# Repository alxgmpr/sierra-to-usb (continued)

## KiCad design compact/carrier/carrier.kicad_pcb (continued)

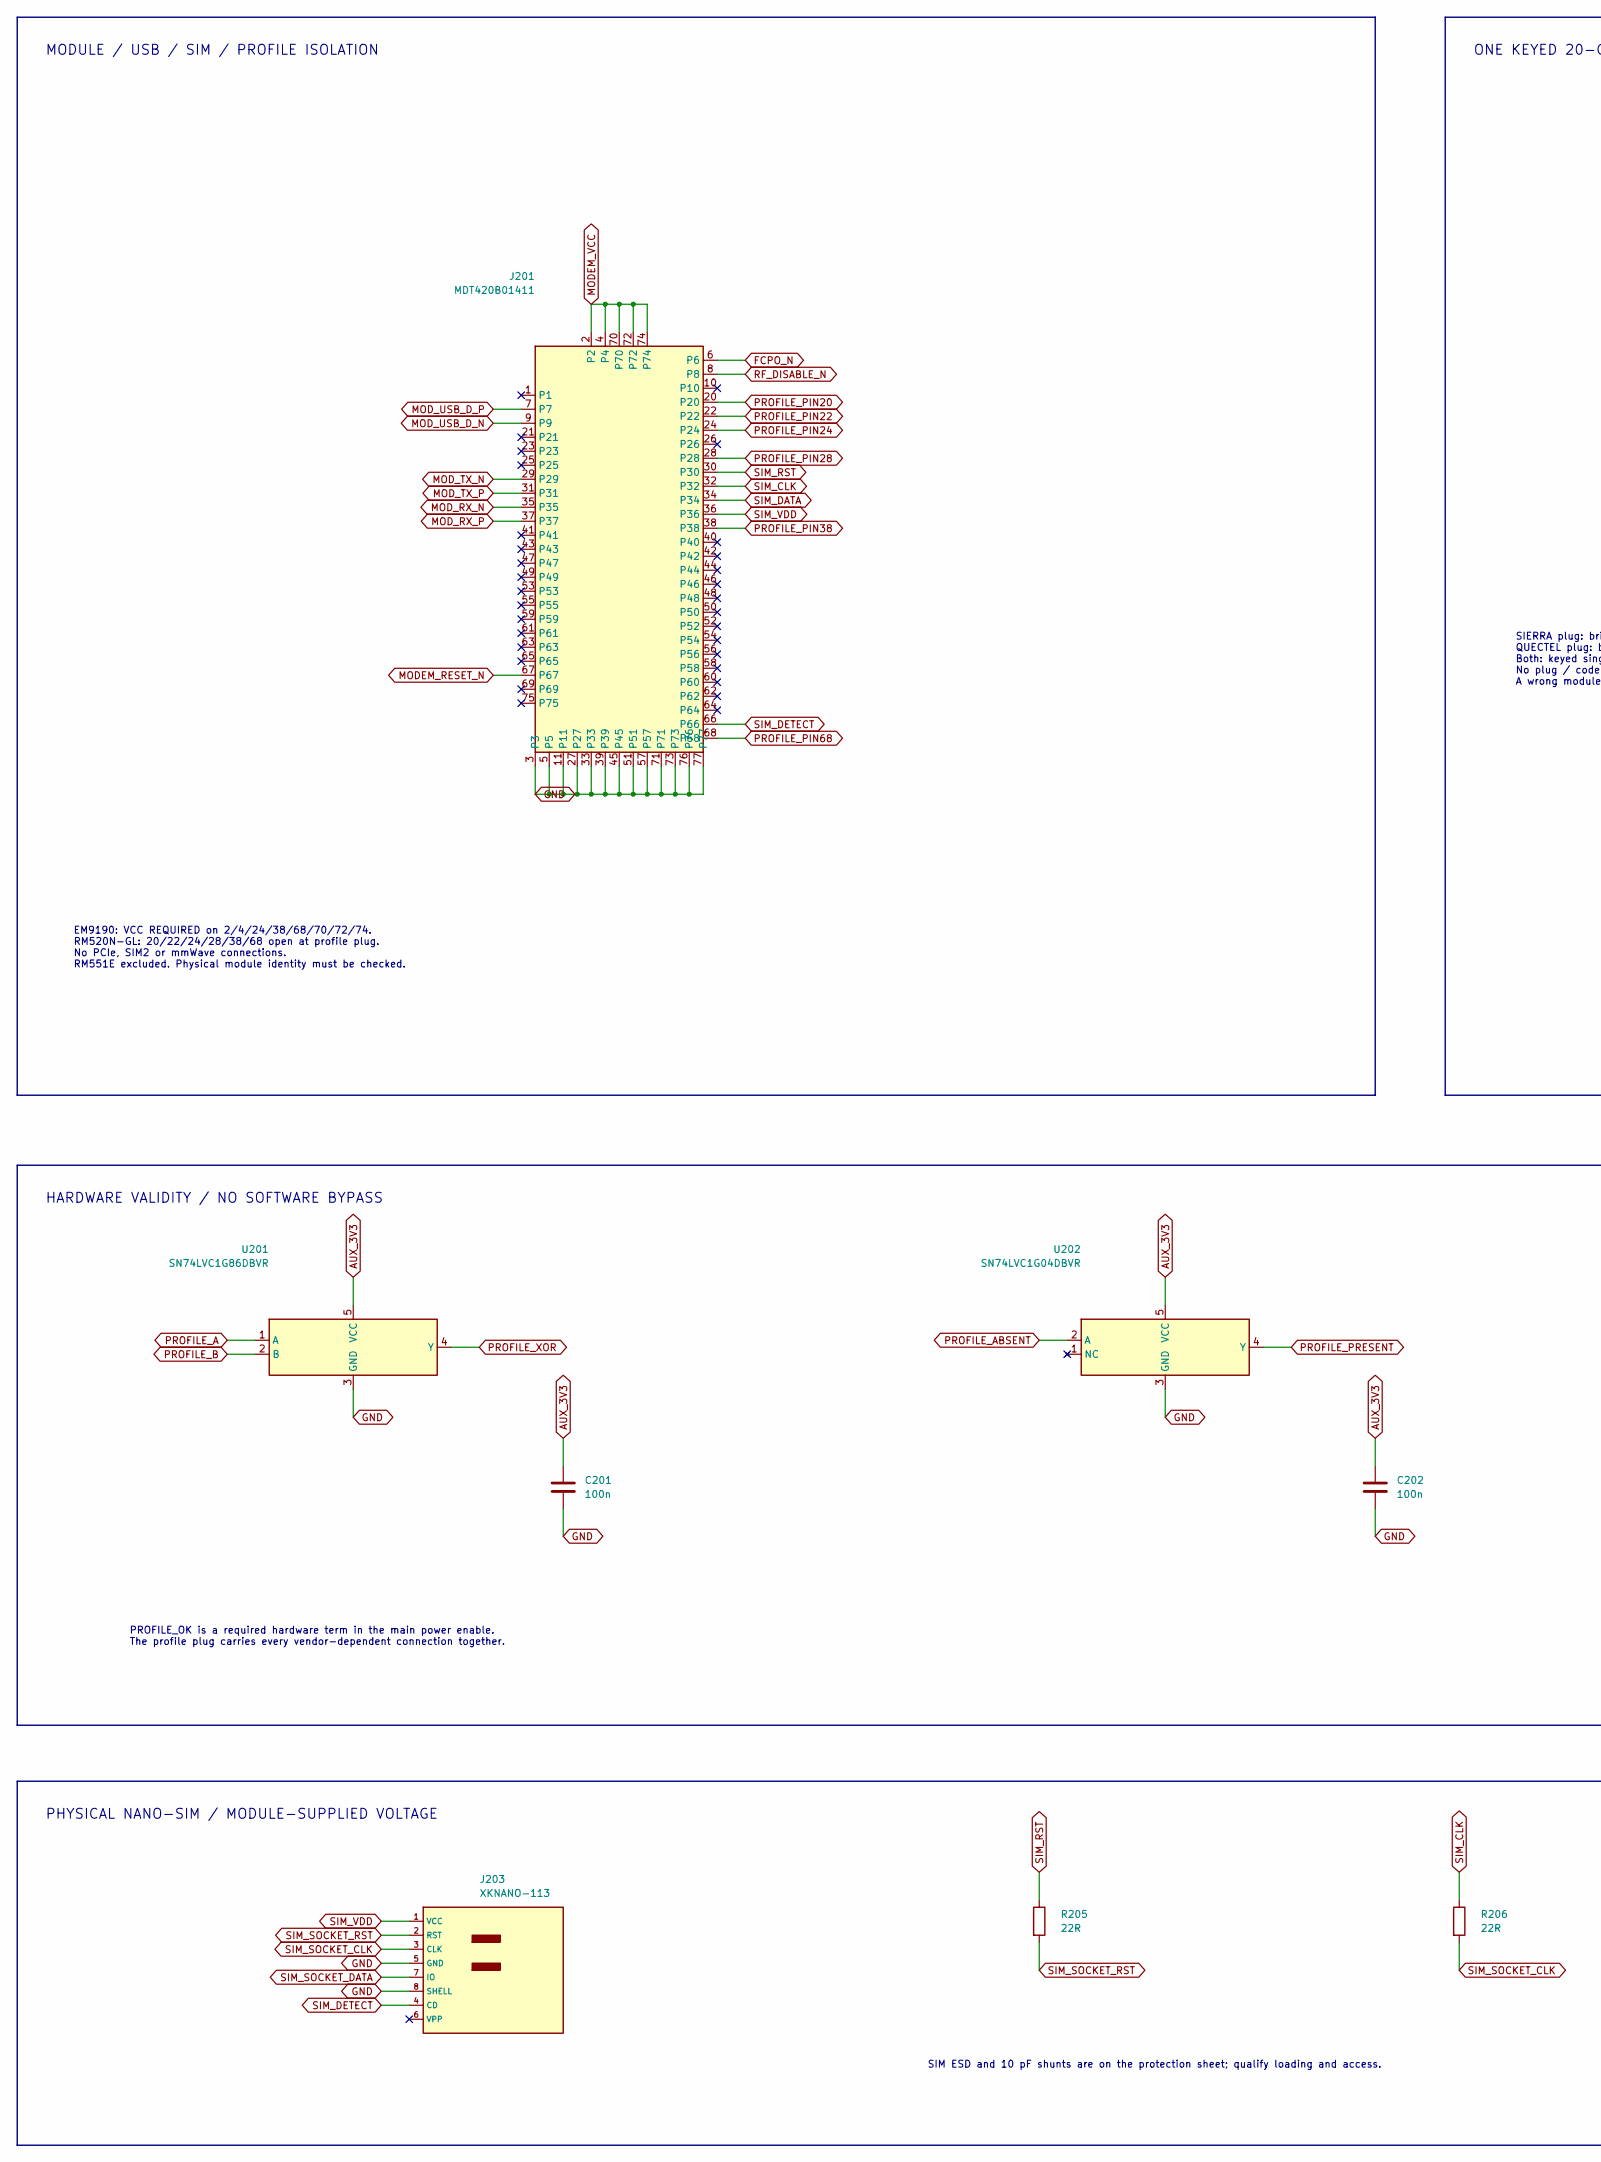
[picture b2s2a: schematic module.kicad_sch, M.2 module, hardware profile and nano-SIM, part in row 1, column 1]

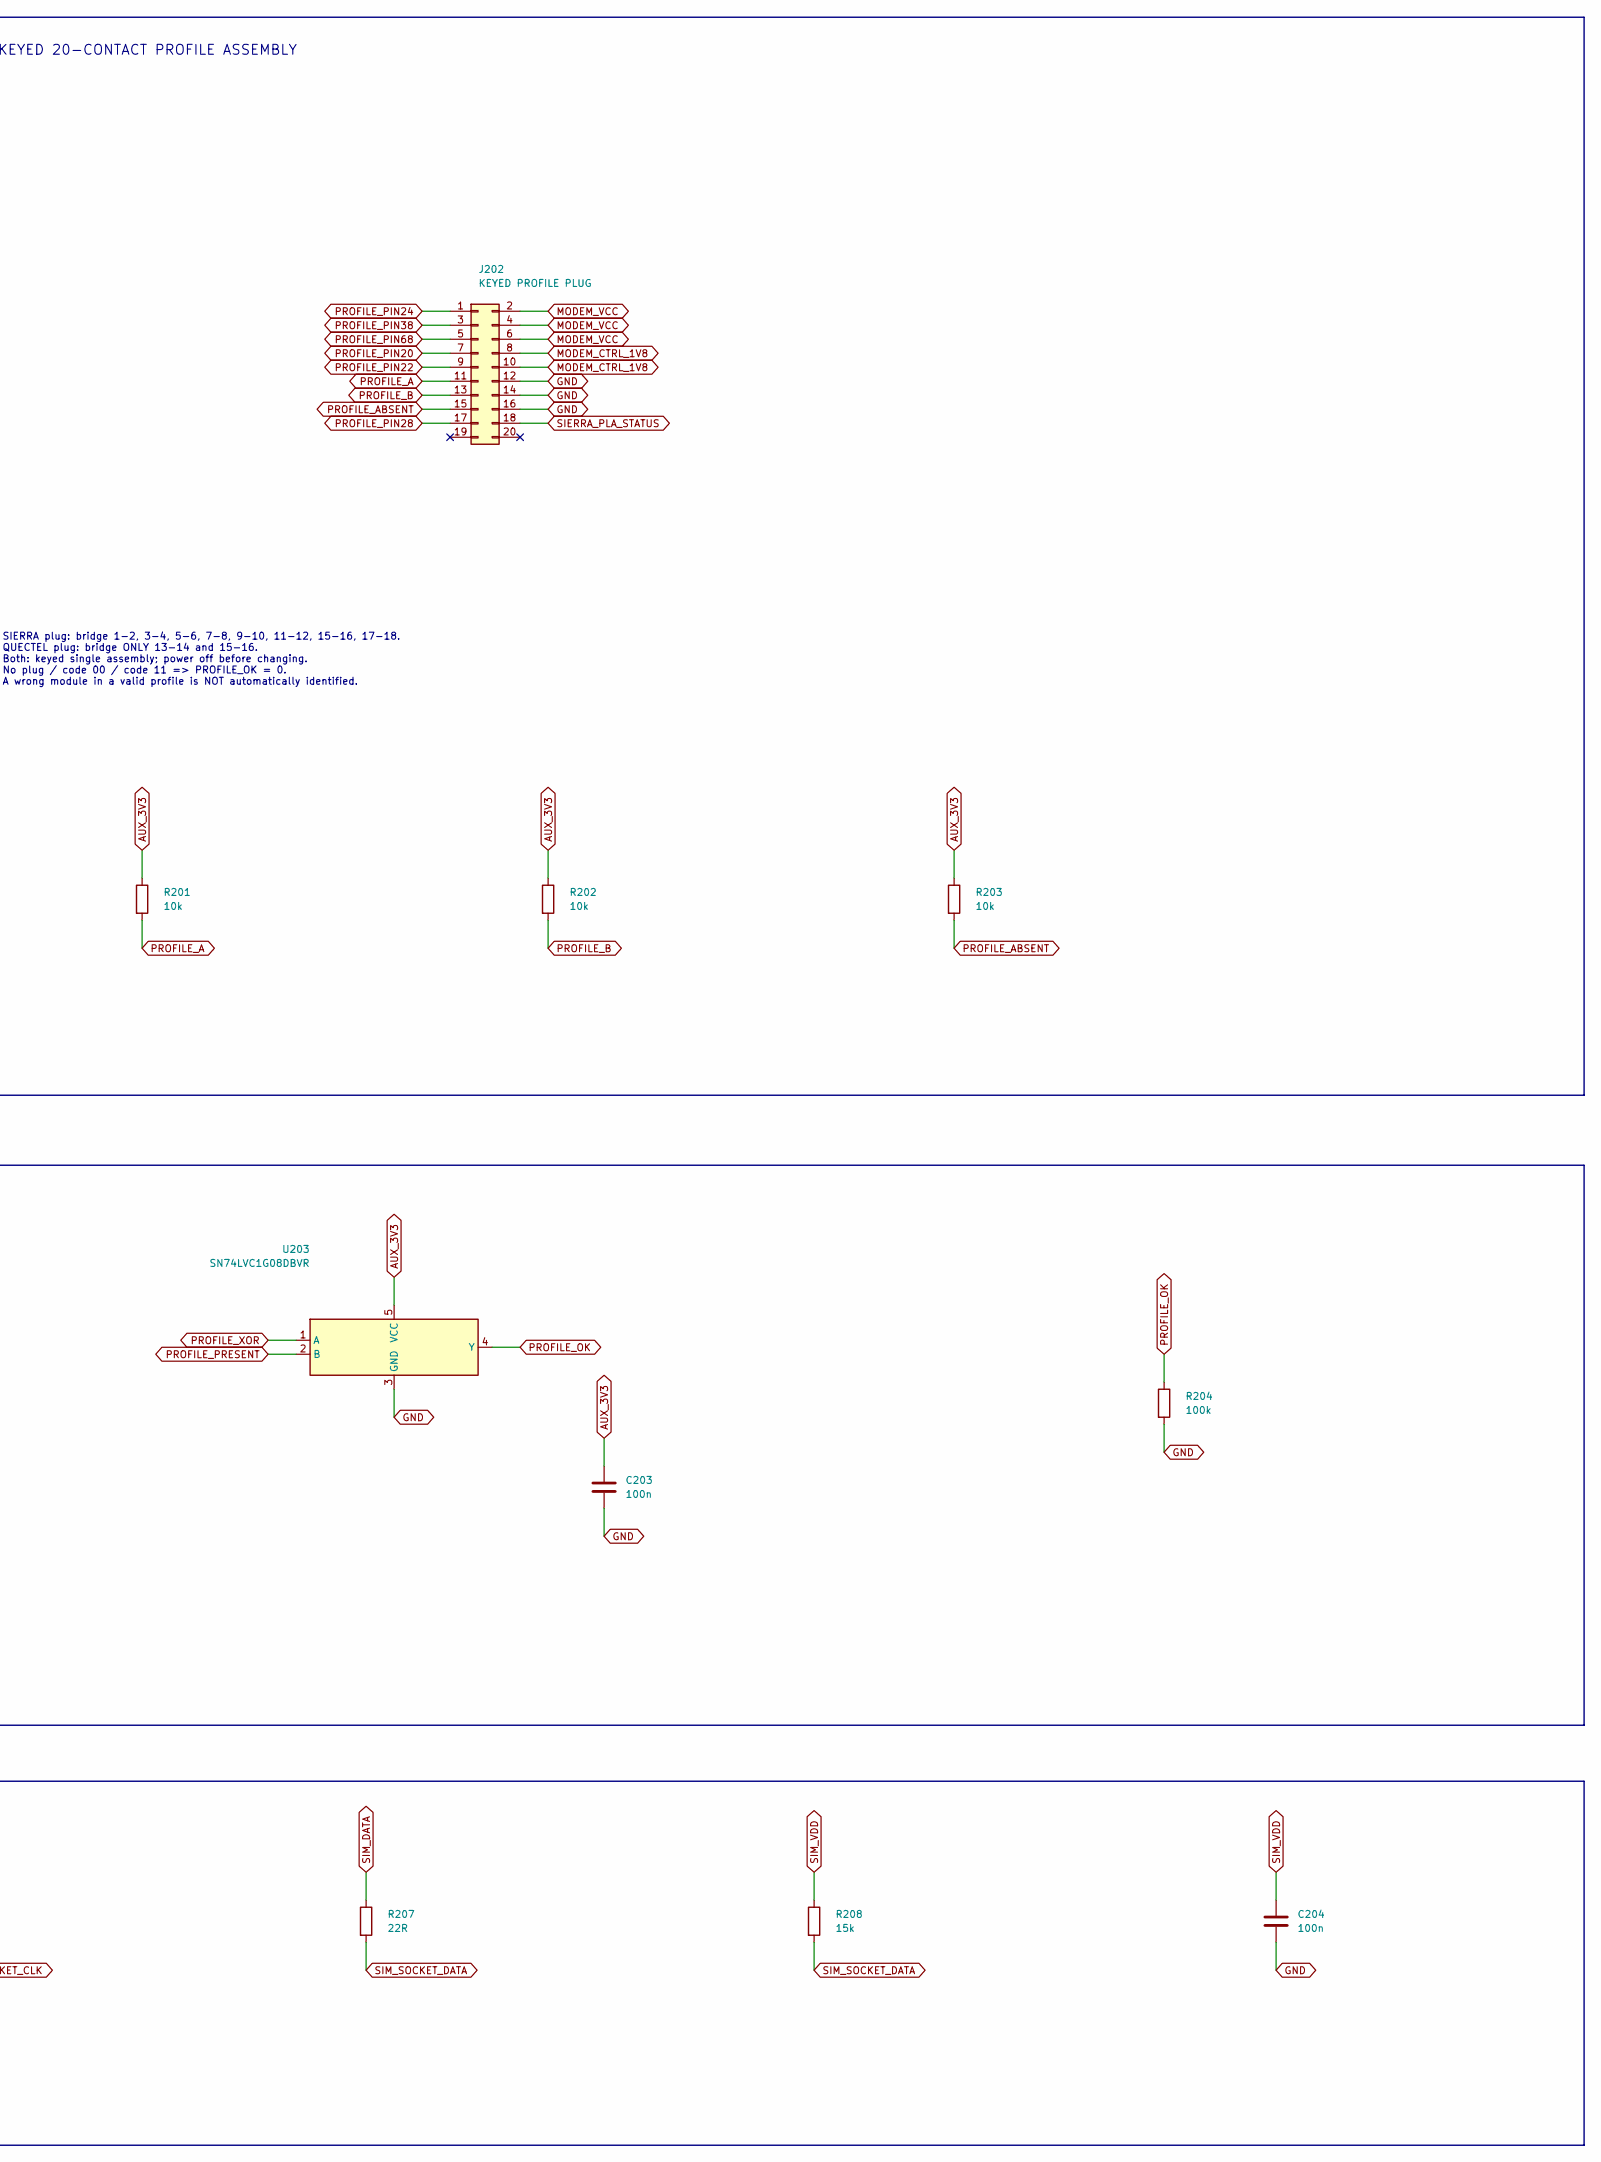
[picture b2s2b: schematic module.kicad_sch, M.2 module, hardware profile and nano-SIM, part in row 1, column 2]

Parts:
C201, C202, C203, C204: 100n; C_0805_2012Metric; MPN C2012X7R1H104K085AA
J201: MDT420B01411; M2_B_Amphenol_MDT420_1A; MPN MDT420B01411
J202: KEYED PROFILE PLUG; IDC_3M_N2520_6002_RB; MPN N2520-6002-RB
J203: XKNANO-113; NanoSIM_XKB_XKNANO-113; MPN XKNANO-113; LCSC C381071
R201, R202, R203: 10k; R_0603_1608Metric; MPN RC0603FR-0710KL
R204: 100k; R_0603_1608Metric; MPN RC0603FR-07100KL
R205, R206, R207: 22R; R_0603_1608Metric; MPN ERJ-3EKF22R0V
R208: 15k; R_0603_1608Metric; MPN RC0603FR-0715KL
U201: SN74LVC1G86DBVR; SOT-23-5; MPN SN74LVC1G86DBVR
U202: SN74LVC1G04DBVR; SOT-23-5; MPN SN74LVC1G04DBVR
U203: SN74LVC1G08DBVR; SOT-23-5; MPN SN74LVC1G08DBVR

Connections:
AUX_3V3: C201.1, C202.1, C203.1, R201.1, R202.1, R203.1, U201.5 (VCC), U202.5 (VCC), U203.5 (VCC); also elsewhere on the board
FCPO_N: J201.6; also elsewhere on the board
GND: C201.2, C202.2, C203.2, C204.2, J201.3, J201.5, J201.11, J201.27, J201.33, J201.39, J201.45, J201.51, J201.57, J201.71, J201.73, J201.76, J201.77, J202.12, J202.14, J202.16, J203.5 (GND), J203.8 (SHELL), R204.2, U201.3 (GND), U202.3 (GND), U203.3 (GND); also elsewhere on the board
MODEM_CTRL_1V8: J202.8, J202.10; also elsewhere on the board
MODEM_RESET_N: J201.67; also elsewhere on the board
MODEM_VCC: J201.2, J201.4, J201.70, J201.72, J201.74, J202.2, J202.4, J202.6; also elsewhere on the board
MOD_RX_N: J201.35; also elsewhere on the board
MOD_RX_P: J201.37; also elsewhere on the board
MOD_TX_N: J201.29; also elsewhere on the board
MOD_TX_P: J201.31; also elsewhere on the board
MOD_USB_D_N: J201.9; also elsewhere on the board
MOD_USB_D_P: J201.7; also elsewhere on the board
PROFILE_A: J202.11, R201.2, U201.1 (A)
PROFILE_ABSENT: J202.15, R203.2, U202.2 (A)
PROFILE_B: J202.13, R202.2, U201.2 (B)
PROFILE_OK: R204.1, U203.4 (Y); also elsewhere on the board
PROFILE_PIN20: J201.20, J202.7
PROFILE_PIN22: J201.22, J202.9
PROFILE_PIN24: J201.24, J202.1
PROFILE_PIN28: J201.28, J202.17
PROFILE_PIN38: J201.38, J202.3
PROFILE_PIN68: J201.68, J202.5
PROFILE_PRESENT: U202.4 (Y), U203.2 (B)
PROFILE_XOR: U201.4 (Y), U203.1 (A)
RF_DISABLE_N: J201.8; also elsewhere on the board
SIERRA_PLA_STATUS: J202.18; also elsewhere on the board
SIM_CLK: J201.32, R206.1
SIM_DATA: J201.34, R207.1
SIM_DETECT: J201.66, J203.4 (CD)
SIM_RST: J201.30, R205.1
SIM_SOCKET_CLK: J203.3 (CLK), R206.2; also elsewhere on the board
SIM_SOCKET_DATA: J203.7 (IO), R207.2, R208.2; also elsewhere on the board
SIM_SOCKET_RST: J203.2 (RST), R205.2; also elsewhere on the board
SIM_VDD: C204.1, J201.36, J203.1 (VCC), R208.1; also elsewhere on the board

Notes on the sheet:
MODULE / USB / SIM / PROFILE ISOLATION
EM9190: VCC REQUIRED on 2/4/24/38/68/70/72/74. RM520N-GL: 20/22/24/28/38/68 open at profile plug. No PCIe, SIM2 or mmWave connections. RM551E excluded. Physical module identity must be checked.
ONE KEYED 20-CONTACT PROFILE ASSEMBLY
SIERRA plug: bridge 1-2, 3-4, 5-6, 7-8, 9-10, 11-12, 15-16, 17-18. QUECTEL plug: bridge ONLY 13-14 and 15-16. Both: keyed single assembly; power off before changing. No plug / code 00 / code 11 => PROFILE_OK = 0. A wrong module in a valid profile is NOT automatically identified.
HARDWARE VALIDITY / NO SOFTWARE BYPASS
PROFILE_OK is a required hardware term in the main power enable. The profile plug carries every vendor-dependent connection together.
PHYSICAL NANO-SIM / MODULE-SUPPLIED VOLTAGE
SIM ESD and 10 pF shunts are on the protection sheet; qualify loading and access.

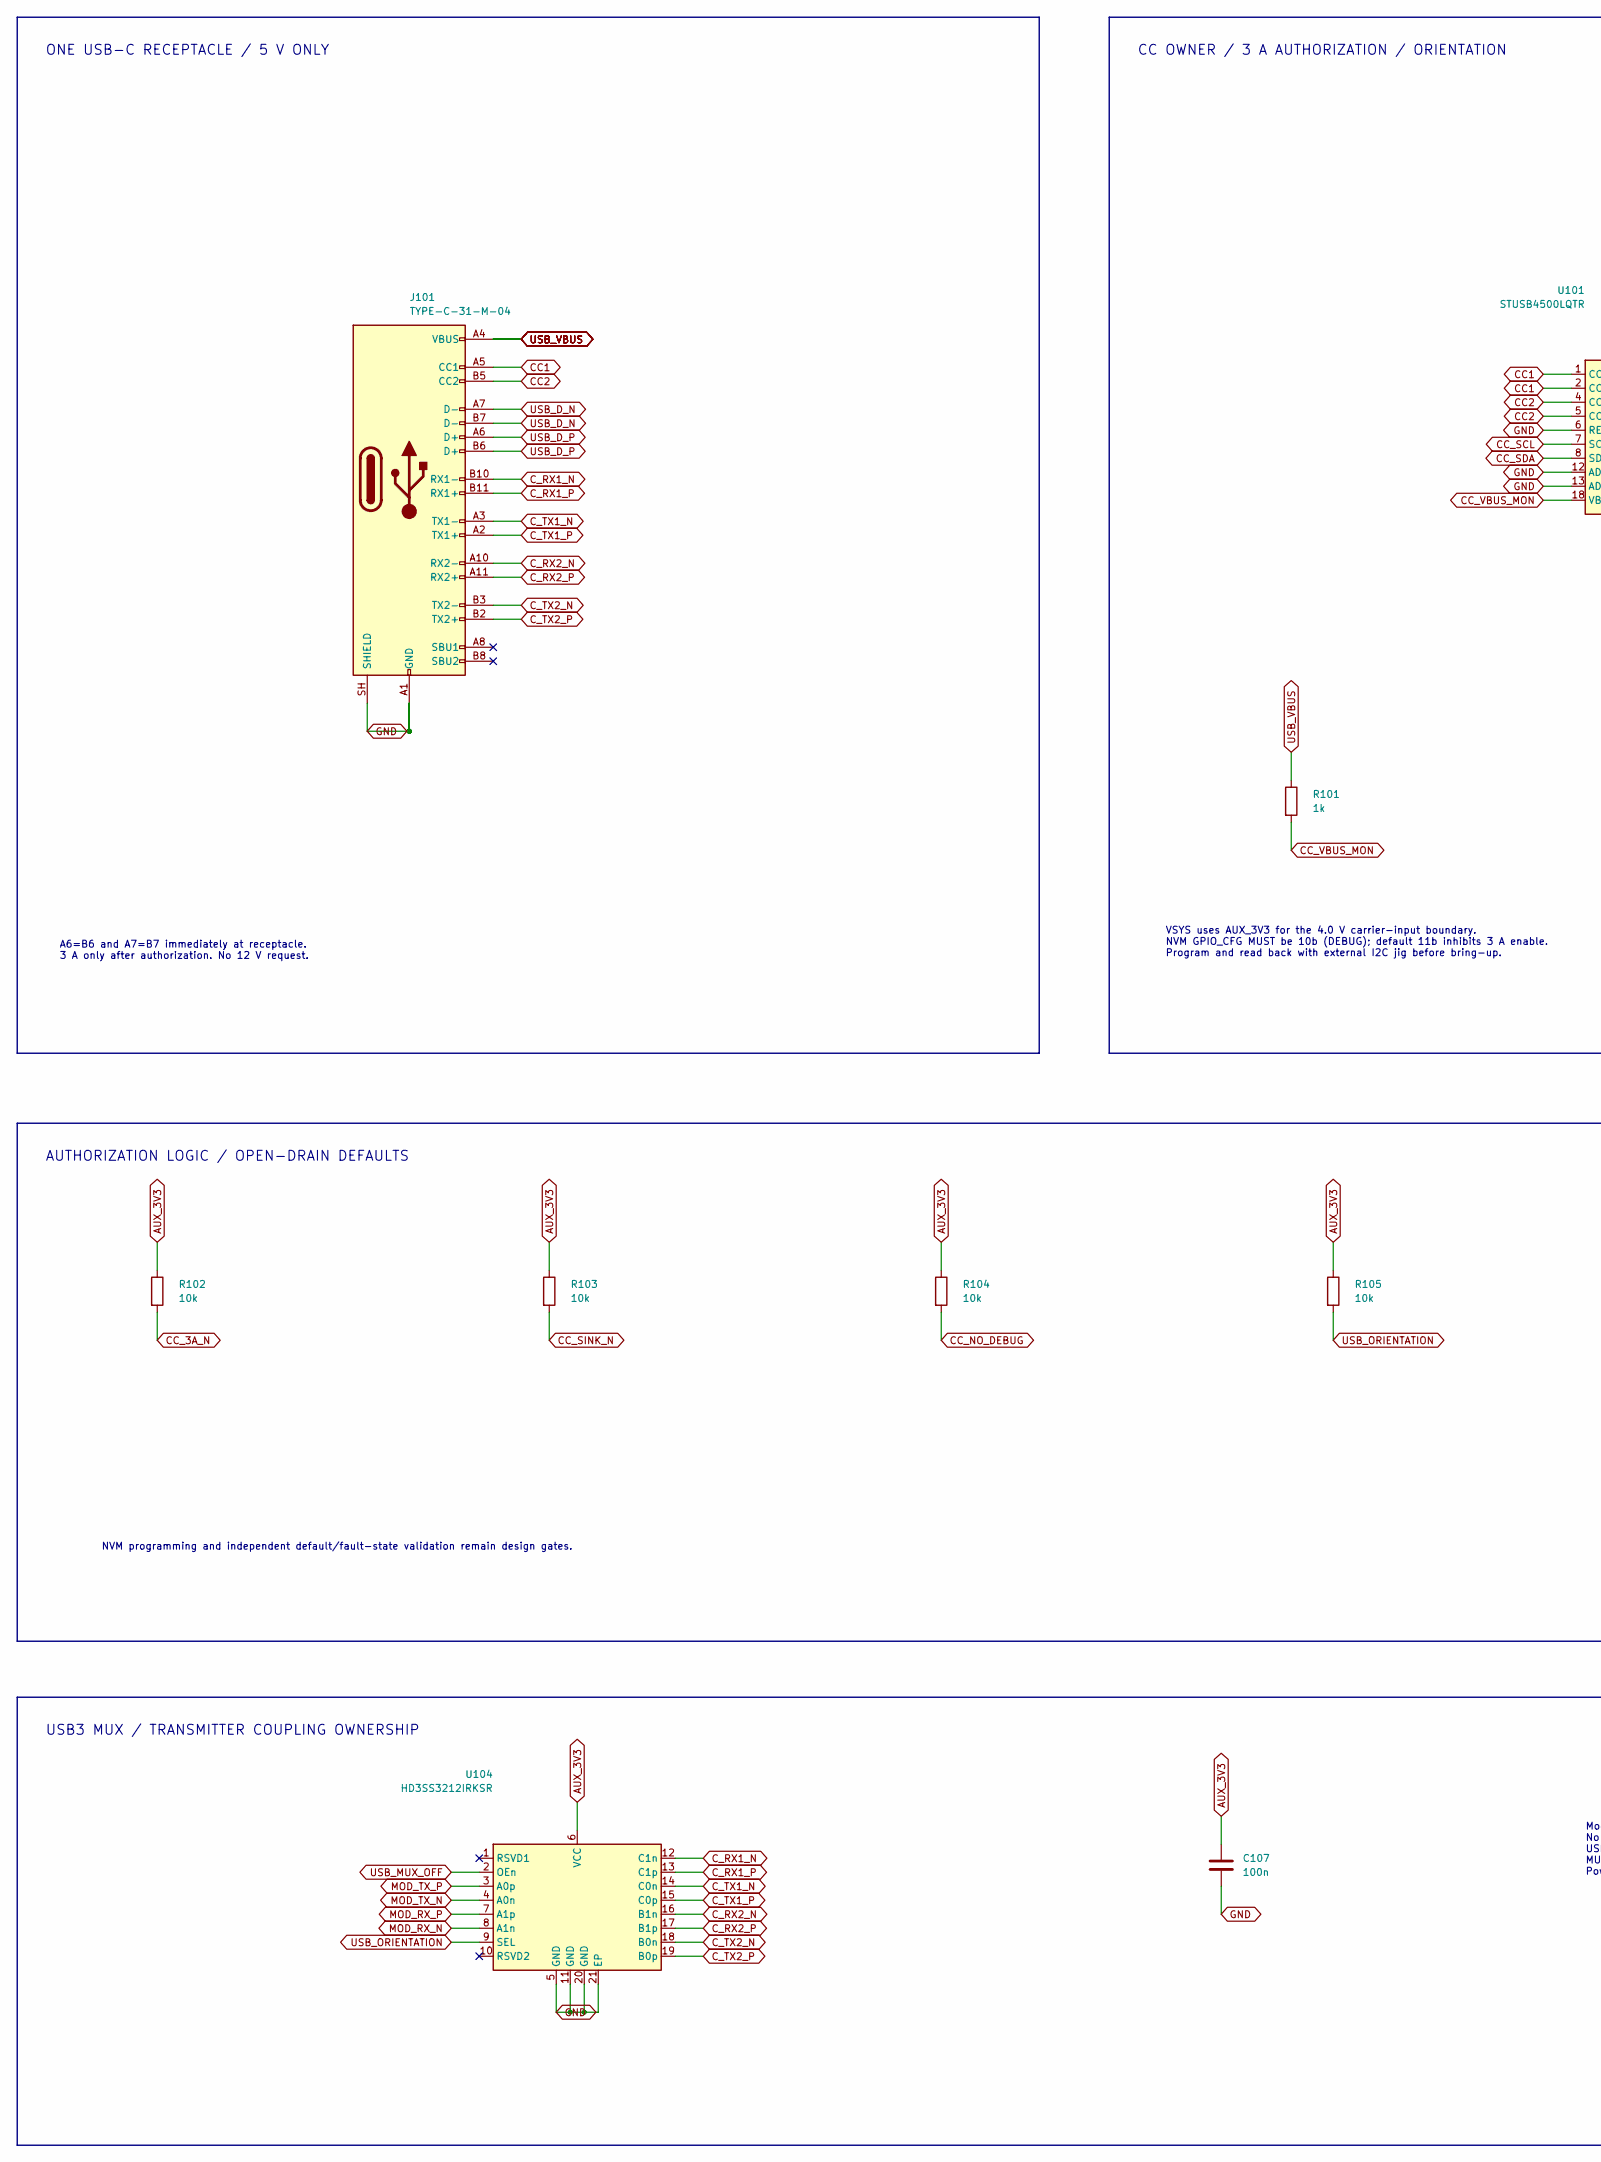
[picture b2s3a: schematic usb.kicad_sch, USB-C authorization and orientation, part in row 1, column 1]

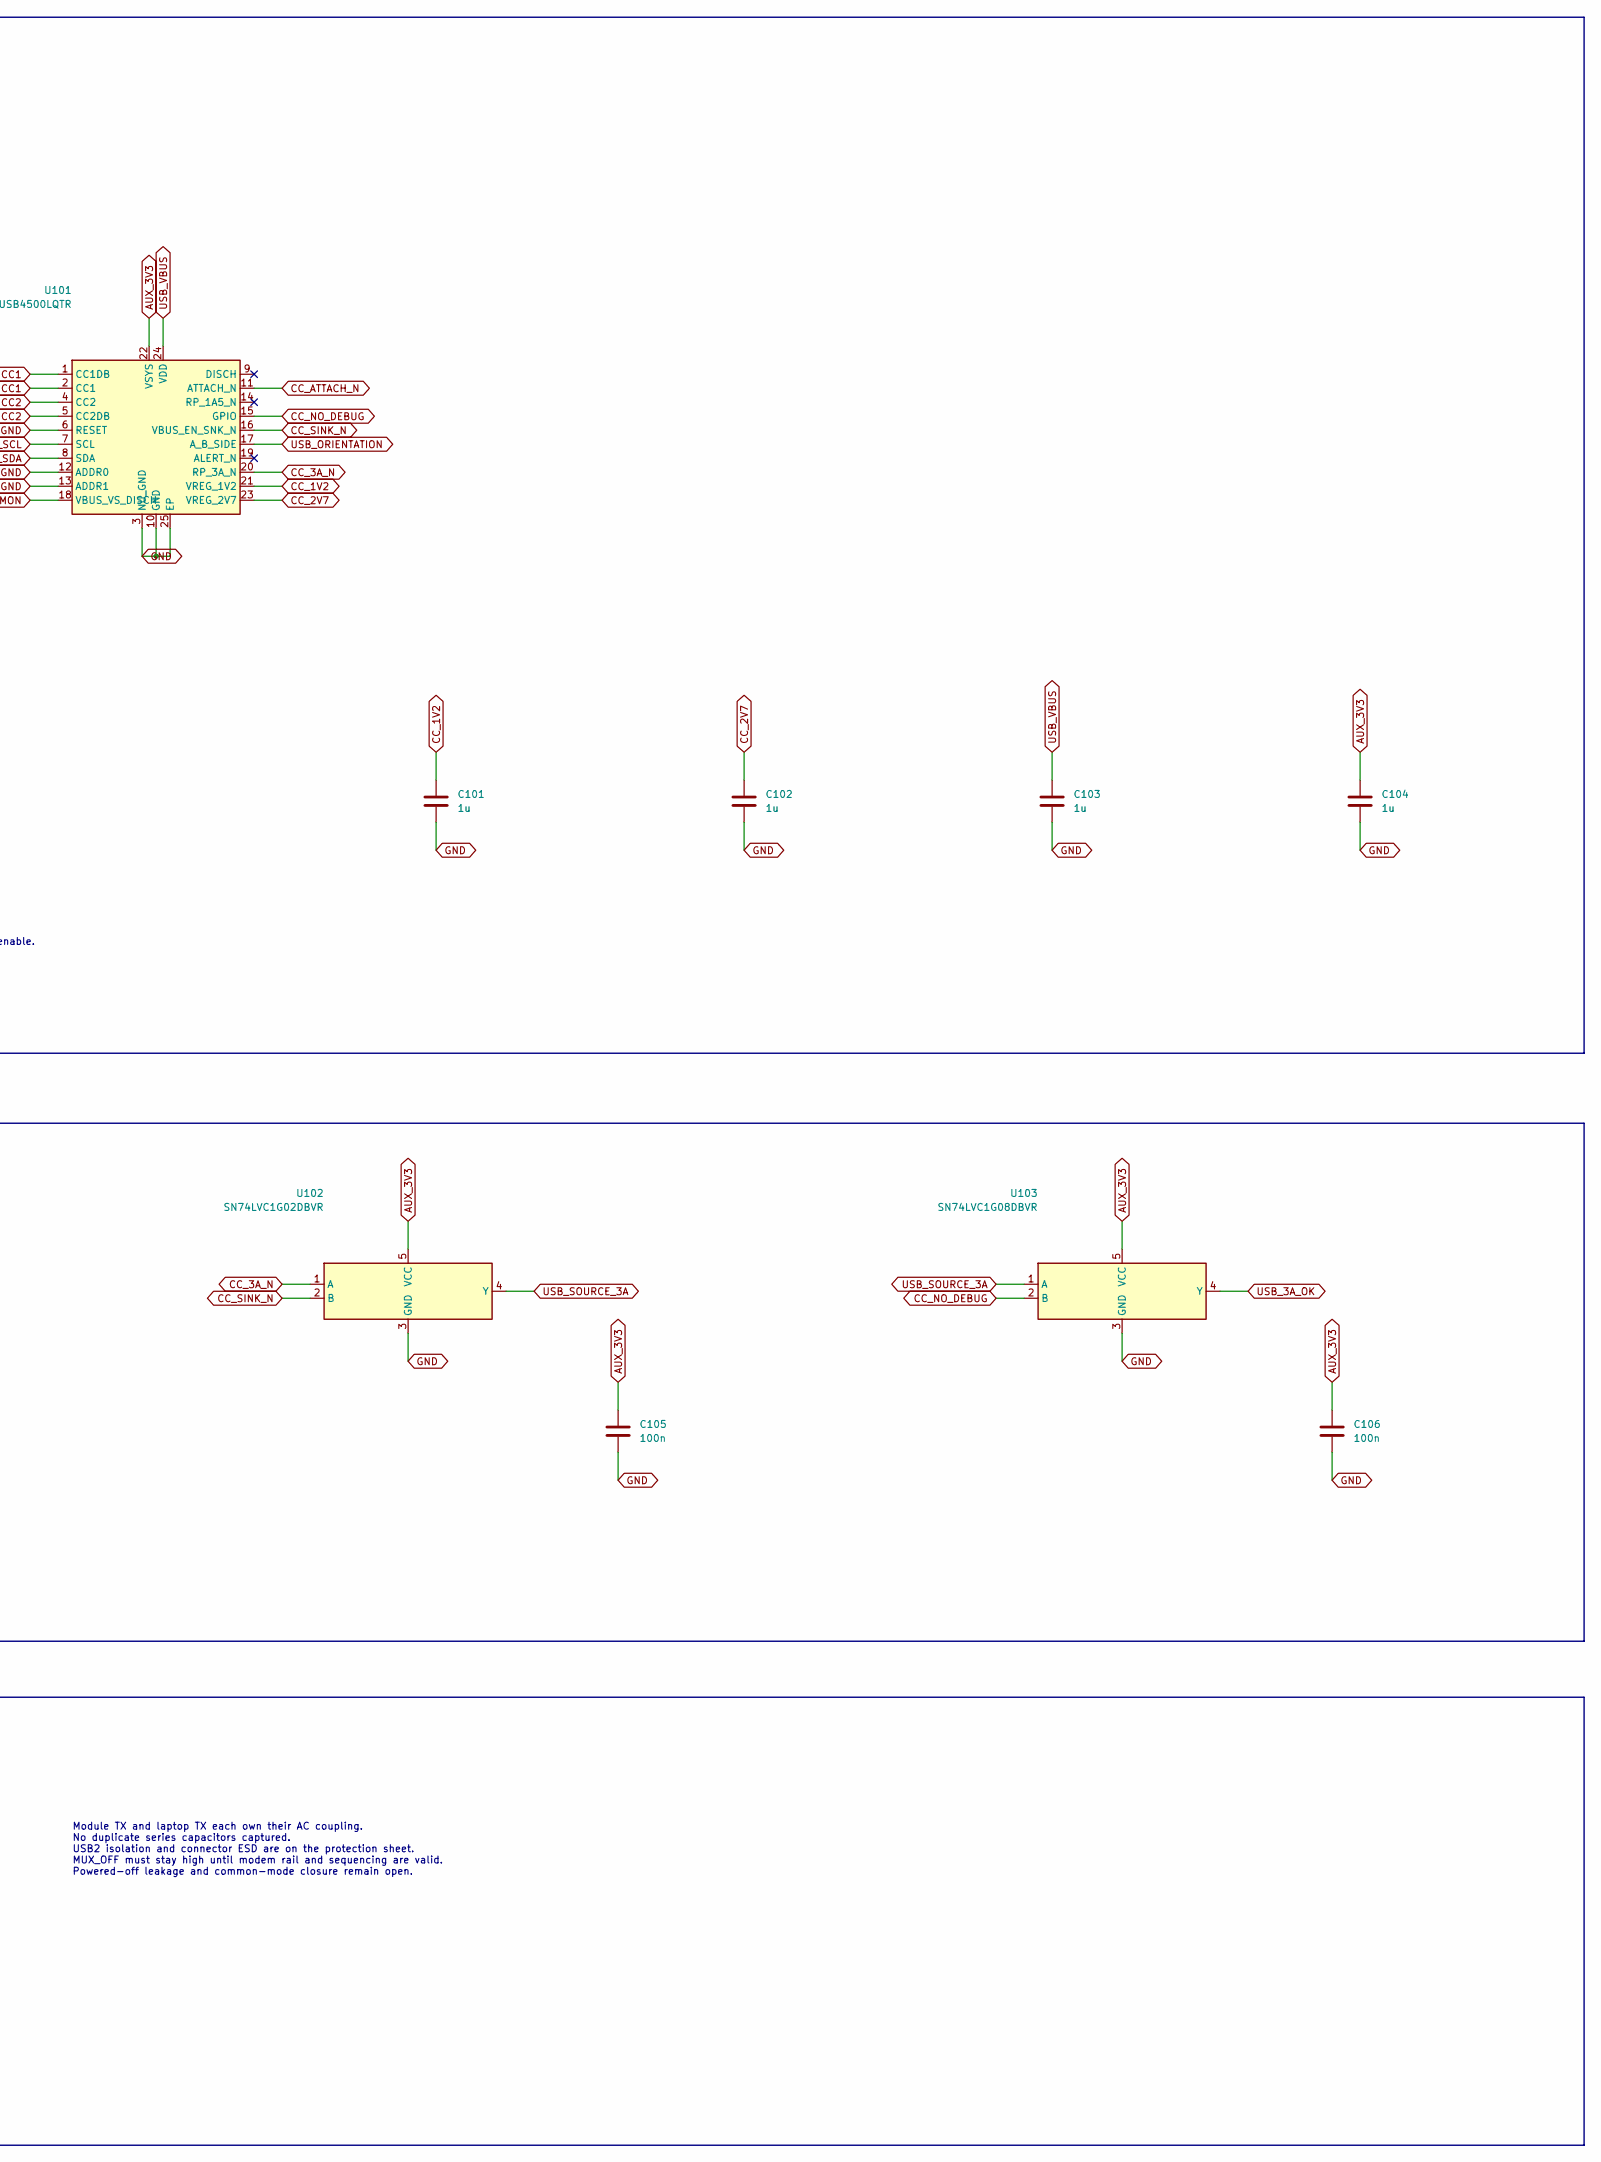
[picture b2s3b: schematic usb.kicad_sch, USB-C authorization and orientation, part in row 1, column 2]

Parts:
C101, C102, C103, C104: 1u; C_1206_3216Metric; MPN C3216X7R1H105K160AB
C105, C106, C107: 100n; C_0805_2012Metric; MPN C2012X7R1H104K085AA
J101: TYPE-C-31-M-04; USB_C_Receptacle_HRO_TYPE-C-31-M-04; MPN TYPE-C-31-M-04; LCSC C129018
R101: 1k; R_0603_1608Metric; MPN RC0603FR-071KL
R102, R103, R104, R105: 10k; R_0603_1608Metric; MPN RC0603FR-0710KL
U101: STUSB4500LQTR; QFN-24-1EP_4x4mm_P0.5mm_EP2.6x2.6mm; MPN STUSB4500LQTR
U102: SN74LVC1G02DBVR; SOT-23-5; MPN SN74LVC1G02DBVR
U103: SN74LVC1G08DBVR; SOT-23-5; MPN SN74LVC1G08DBVR
U104: HD3SS3212IRKSR; WQFN-20-1EP_2.5x4.5mm_P0.5mm_EP1x2.9mm; MPN HD3SS3212IRKSR

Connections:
AUX_3V3: C104.1, C105.1, C106.1, C107.1, R102.1, R103.1, R104.1, R105.1, U101.22 (VSYS), U102.5 (VCC), U103.5 (VCC), U104.6 (VCC); also elsewhere on the board
CC1: J101.A5 (CC1), U101.1 (CC1DB), U101.2 (CC1); also elsewhere on the board
CC2: J101.B5 (CC2), U101.4 (CC2), U101.5 (CC2DB); also elsewhere on the board
CC_1V2: C101.1, U101.21 (VREG_1V2)
CC_2V7: C102.1, U101.23 (VREG_2V7)
CC_3A_N: R102.2, U101.20 (RP_3A_N), U102.1 (A)
CC_ATTACH_N: U101.11 (ATTACH_N); also elsewhere on the board
CC_NO_DEBUG: R104.2, U101.15 (GPIO), U103.2 (B)
CC_SCL: U101.7 (SCL); also elsewhere on the board
CC_SDA: U101.8 (SDA); also elsewhere on the board
CC_SINK_N: R103.2, U101.16 (VBUS_EN_SNK_N), U102.2 (B)
CC_VBUS_MON: R101.2, U101.18 (VBUS_VS_DISCH)
C_RX1_N: J101.B10 (RX1-), U104.12 (C1n); also elsewhere on the board
C_RX1_P: J101.B11 (RX1+), U104.13 (C1p); also elsewhere on the board
C_RX2_N: J101.A10 (RX2-), U104.16 (B1n); also elsewhere on the board
C_RX2_P: J101.A11 (RX2+), U104.17 (B1p); also elsewhere on the board
C_TX1_N: J101.A3 (TX1-), U104.14 (C0n); also elsewhere on the board
C_TX1_P: J101.A2 (TX1+), U104.15 (C0p); also elsewhere on the board
C_TX2_N: J101.B3 (TX2-), U104.18 (B0n); also elsewhere on the board
C_TX2_P: J101.B2 (TX2+), U104.19 (B0p); also elsewhere on the board
GND: C101.2, C102.2, C103.2, C104.2, C105.2, C106.2, C107.2, J101.A1 (GND), J101.A12 (GND), J101.B1 (GND), J101.B12 (GND), J101.SH (SHIELD), U101.3 (NU_GND), U101.6 (RESET), U101.10 (GND), U101.12 (ADDR0), U101.13 (ADDR1), U101.25 (EP), U102.3 (GND), U103.3 (GND), U104.5 (GND), U104.11 (GND), U104.20 (GND), U104.21 (EP); also elsewhere on the board
MOD_RX_N: U104.8 (A1n); also elsewhere on the board
MOD_RX_P: U104.7 (A1p); also elsewhere on the board
MOD_TX_N: U104.4 (A0n); also elsewhere on the board
MOD_TX_P: U104.3 (A0p); also elsewhere on the board
USB_3A_OK: U103.4 (Y); also elsewhere on the board
USB_D_N: J101.A7 (D-), J101.B7 (D-); also elsewhere on the board
USB_D_P: J101.A6 (D+), J101.B6 (D+); also elsewhere on the board
USB_MUX_OFF: U104.2 (OEn); also elsewhere on the board
USB_ORIENTATION: R105.2, U101.17 (A_B_SIDE), U104.9 (SEL)
USB_SOURCE_3A: U102.4 (Y), U103.1 (A)
USB_VBUS: C103.1, J101.A4 (VBUS), J101.A9 (VBUS), J101.B4 (VBUS), J101.B9 (VBUS), R101.1, U101.24 (VDD); also elsewhere on the board

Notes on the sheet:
ONE USB-C RECEPTACLE / 5 V ONLY
A6=B6 and A7=B7 immediately at receptacle. 3 A only after authorization. No 12 V request.
CC OWNER / 3 A AUTHORIZATION / ORIENTATION
VSYS uses AUX_3V3 for the 4.0 V carrier-input boundary. NVM GPIO_CFG MUST be 10b (DEBUG); default 11b inhibits 3 A enable. Program and read back with external I2C jig before bring-up.
AUTHORIZATION LOGIC / OPEN-DRAIN DEFAULTS
NVM programming and independent default/fault-state validation remain design gates.
USB3 MUX / TRANSMITTER COUPLING OWNERSHIP
Module TX and laptop TX each own their AC coupling. No duplicate series capacitors captured. USB2 isolation and connector ESD are on the protection sheet. MUX_OFF must stay high until modem rail and sequencing are valid. Powered-off leakage and common-mode closure remain open.
